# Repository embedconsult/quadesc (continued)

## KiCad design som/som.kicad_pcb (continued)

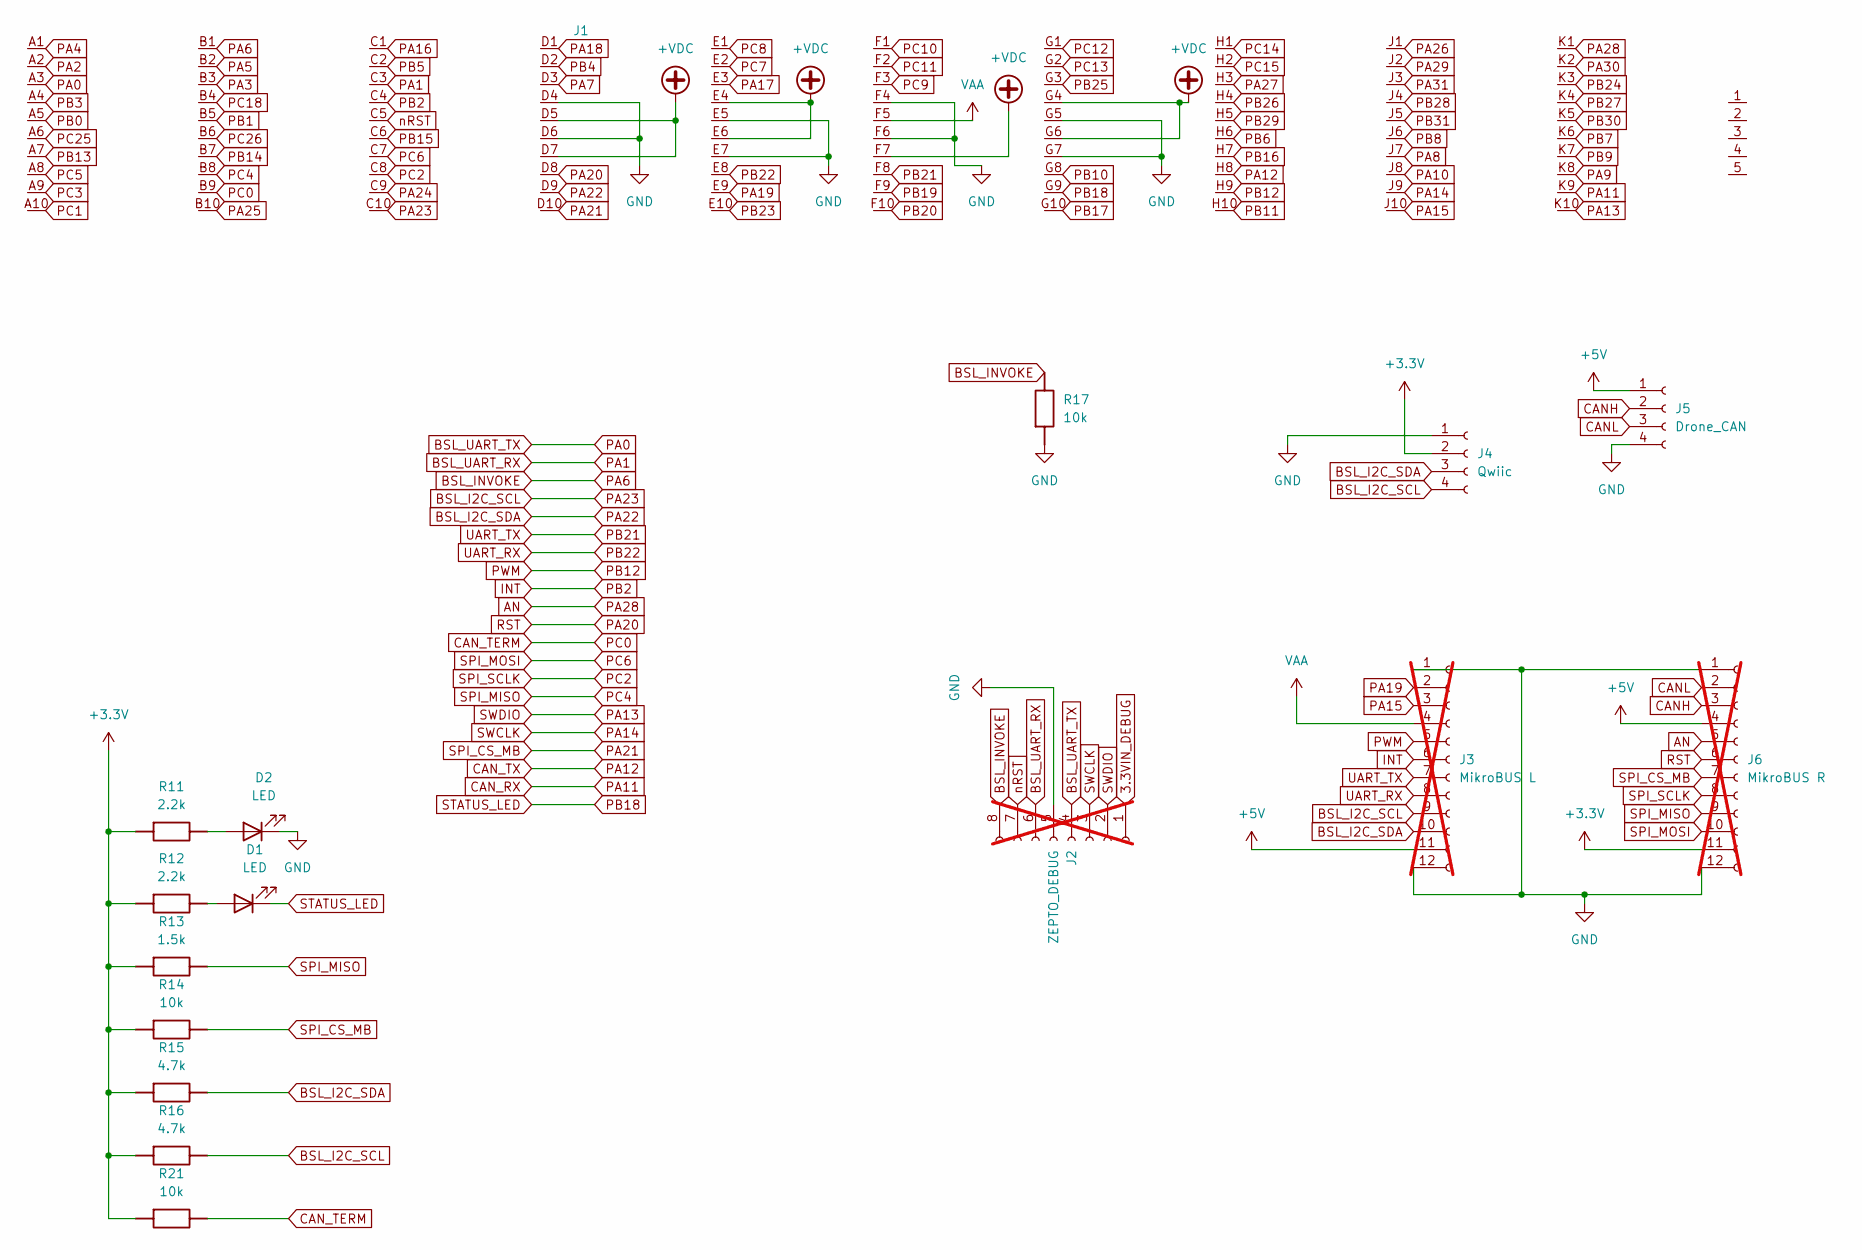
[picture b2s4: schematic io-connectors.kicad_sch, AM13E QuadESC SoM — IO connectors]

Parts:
D1, D2: LED; LED_0402_1005Metric
J1: LGA-100_10x10_14.0x14.0mm
J2: ZEPTO_DEBUG; PinHeader_1x08_P2.54mm_Vertical; not fitted
J3: MikroBUS L; not fitted
J4: Qwiic; CONN_SM04B-SRSS-TB_JST
J5: Drone_CAN; JST_SM04B-GHS-TB
J6: MikroBUS R; not fitted
R11, R12: 2.2k; R_0201_0603Metric
R13: 1.5k; R_0201_0603Metric
R14, R17, R21: 10k; R_0201_0603Metric
R15, R16: 4.7k; R_0201_0603Metric

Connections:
3.3VIN_DEBUG: J2.1; also elsewhere on the board
+3.3V: J4.2, J6.11, R11.1, R12.1, R13.1, R14.1, R15.1, R16.1, R21.1; also elsewhere on the board
+5V: J3.11, J5.1, J6.4; also elsewhere on the board
+VDC: J1.D5, J1.D7, J1.E4, J1.E6, J1.F7, J1.G4, J1.G6; also elsewhere on the board
AN: J1.K1, J6.5; also elsewhere on the board
BSL_I2C_SCL: J1.C10, J3.9, J4.4, R16.2; also elsewhere on the board
BSL_I2C_SDA: J1.D9, J3.10, J4.3, R15.2; also elsewhere on the board
BSL_INVOKE: J1.B1, J2.8, R17.2; also elsewhere on the board
BSL_UART_RX: J1.C3, J2.6; also elsewhere on the board
BSL_UART_TX: J1.A3, J2.4; also elsewhere on the board
CANH: J5.2, J6.3; also elsewhere on the board
CANL: J5.3, J6.2; also elsewhere on the board
CAN_RX: J1.K9; also elsewhere on the board
CAN_TERM: J1.B9, R21.2; also elsewhere on the board
CAN_TX: J1.H8; also elsewhere on the board
GND: D2.1 (K), J1.D4, J1.D6, J1.E5, J1.E7, J1.F4, J1.F6, J1.G5, J1.G7, J2.5, J3.1, J3.12, J4.1, J5.4, J6.1, J6.12, R17.1; also elsewhere on the board
INT: J1.C4, J3.6; also elsewhere on the board
unnamed: D1.2 (A), R12.2
unnamed: D2.2 (A), R11.2
PA2: J1.A2; also elsewhere on the board
PA3: J1.B3; also elsewhere on the board
PA4: J1.A1; also elsewhere on the board
PA5: J1.B2; also elsewhere on the board
PA7: J1.D3; also elsewhere on the board
PA8: J1.J7; also elsewhere on the board
PA9: J1.K8; also elsewhere on the board
PA10: J1.J8; also elsewhere on the board
PA13: J1.K10, J2.2; also elsewhere on the board
PA14: J1.J9, J2.3; also elsewhere on the board
PA15: J1.J10, J3.3; also elsewhere on the board
PA16: J1.C1; also elsewhere on the board
PA17: J1.E3; also elsewhere on the board
PA18: J1.D1; also elsewhere on the board
PA19: J1.E9, J3.2; also elsewhere on the board
PA20: J1.D8, J6.6; also elsewhere on the board
PA21: J1.D10, J6.7, R14.2; also elsewhere on the board
PA24: J1.C9; also elsewhere on the board
PA25: J1.B10; also elsewhere on the board
PA26: J1.J1; also elsewhere on the board
PA27: J1.H3; also elsewhere on the board
PA29: J1.J2; also elsewhere on the board
PA30: J1.K2; also elsewhere on the board
PA31: J1.J3; also elsewhere on the board
PB0: J1.A5; also elsewhere on the board
PB1: J1.B5; also elsewhere on the board
PB3: J1.A4; also elsewhere on the board
PB4: J1.D2; also elsewhere on the board
PB5: J1.C2; also elsewhere on the board
PB6: J1.H6; also elsewhere on the board
PB7: J1.K6; also elsewhere on the board
PB8: J1.J6; also elsewhere on the board
PB9: J1.K7; also elsewhere on the board
PB10: J1.G8; also elsewhere on the board
PB11: J1.H10; also elsewhere on the board
PB12: J1.H9, J3.5; also elsewhere on the board
PB13: J1.A7; also elsewhere on the board
PB14: J1.B7; also elsewhere on the board
PB15: J1.C6; also elsewhere on the board
PB16: J1.H7; also elsewhere on the board
PB17: J1.G10; also elsewhere on the board
PB18: D1.1 (K), J1.G9; also elsewhere on the board
PB19: J1.F9; also elsewhere on the board
PB20: J1.F10; also elsewhere on the board
PB21: J1.F8, J3.7; also elsewhere on the board
PB22: J1.E8, J3.8; also elsewhere on the board
PB23: J1.E10; also elsewhere on the board
PB24: J1.K3; also elsewhere on the board
PB25: J1.G3; also elsewhere on the board
PB26: J1.H4; also elsewhere on the board
PB27: J1.K4; also elsewhere on the board
PB28: J1.J4; also elsewhere on the board
PB29: J1.H5; also elsewhere on the board
PB30: J1.K5; also elsewhere on the board
PB31: J1.J5; also elsewhere on the board
PC1: J1.A10; also elsewhere on the board
PC2: J1.C8, J6.8; also elsewhere on the board
PC3: J1.A9; also elsewhere on the board
PC4: J1.B8, J6.9, R13.2; also elsewhere on the board
PC5: J1.A8; also elsewhere on the board
PC6: J1.C7, J6.10; also elsewhere on the board
PC7: J1.E2; also elsewhere on the board
PC8: J1.E1; also elsewhere on the board
PC9: J1.F3; also elsewhere on the board
PC10: J1.F1; also elsewhere on the board
PC11: J1.F2; also elsewhere on the board
PC12: J1.G1; also elsewhere on the board
PC13: J1.G2; also elsewhere on the board
PC14: J1.H1; also elsewhere on the board
PC15: J1.H2; also elsewhere on the board
PC18: J1.B4; also elsewhere on the board
PC25: J1.A6; also elsewhere on the board
PC26: J1.B6; also elsewhere on the board
VAA: J1.F5, J3.4; also elsewhere on the board
nRST: J1.C5, J2.7; also elsewhere on the board

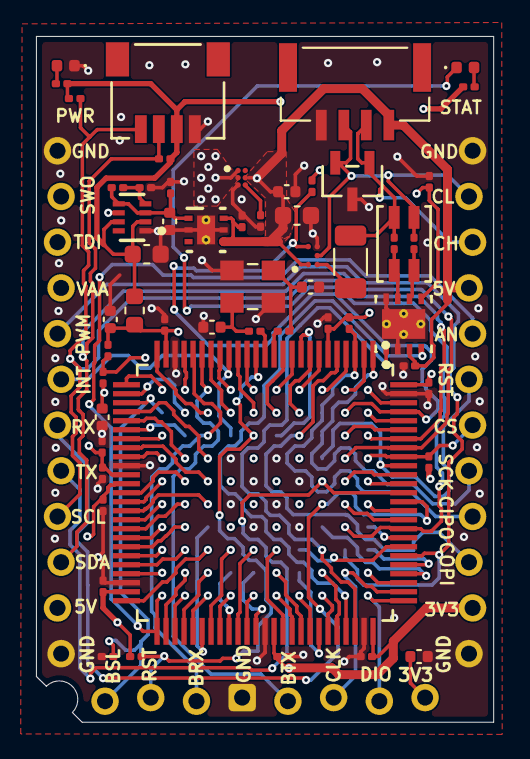
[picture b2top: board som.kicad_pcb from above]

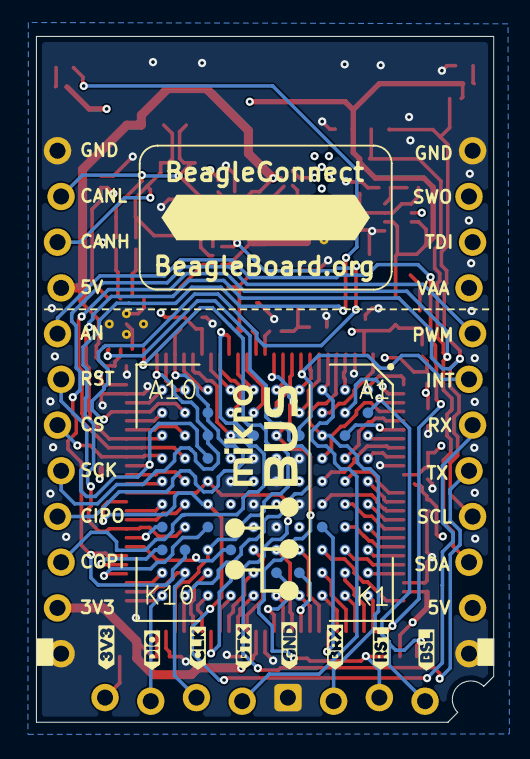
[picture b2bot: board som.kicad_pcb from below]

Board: 4 copper layers, 25.4 x 38.1 mm, 68 parts (10 on the bottom side), 106 nets.

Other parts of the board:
kibuzzard-698ADC7E: G***; kibuzzard-698ADC7E
kibuzzard-698ADC8D: G***; kibuzzard-698ADC8D
kibuzzard-698ADC75: G***; kibuzzard-698ADC75
kibuzzard-698ADC83: G***; kibuzzard-698ADC83
kibuzzard-698ADC88: G***; kibuzzard-698ADC88
kibuzzard-698ADC92: G***; kibuzzard-698ADC92
kibuzzard-698ADC96: G***; kibuzzard-698ADC96
kibuzzard-698AE4C9: G***; kibuzzard-698AE4C9
kibuzzard-698CA76F: G***; kibuzzard-698CA76F

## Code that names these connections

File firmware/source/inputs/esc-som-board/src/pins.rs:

//! Wiring extracted from corrected source 802aacd, current SysConfig v3 authority.
//! Package/mux evidence is recorded separately; chip Pin contains only port/bit.
use am13_rs::gpio::{
    Pin,
    Port::{A, B, C},
};
pub const BSL_UART_TX: Pin = Pin::new(A, 0);
pub const BSL_UART_RX: Pin = Pin::new(A, 1);
pub const BSL_CAN_TX: Pin = Pin::new(A, 12);
pub const BSL_CAN_RX: Pin = Pin::new(A, 11);
pub const BSL_INVOKE: Pin = Pin::new(A, 6);
pub const DRV_ENABLE: Pin = Pin::new(B, 10);
pub const INL_ENABLE: Pin = Pin::new(B, 11);
pub const STATUS_LED: Pin = Pin::new(B, 18);
pub const CAN_TERM: Pin = Pin::new(B, 9);
pub const I2C_SDA: Pin = Pin::new(A, 22);
pub const I2C_SCL: Pin = Pin::new(A, 23);
pub const SPI_MOSI: Pin = Pin::new(C, 6);
pub const SPI_MISO: Pin = Pin::new(C, 4);
pub const SPI_SCLK: Pin = Pin::new(C, 2);
pub const NFAULT: [Pin; 4] = [
    Pin::new(A, 30),
    Pin::new(B, 15),
    Pin::new(B, 17),
    Pin::new(B, 0),
];
pub const DRIVER_CS: [Pin; 4] = [
    Pin::new(C, 13),
    Pin::new(B, 14),
    Pin::new(B, 16),
    Pin::new(C, 5),
];

/// All motor PWM pads from v3, including the extra Motor1 3B output.
/// LED-cal holds these as GPIO-low; it never selects the PWM mux.
pub const MOTOR_OUTPUTS: [Pin; 13] = [
    Pin::new(B, 6),
    Pin::new(B, 7),
    Pin::new(B, 8),
    Pin::new(B, 12),
    Pin::new(C, 25),
    Pin::new(C, 26),
    Pin::new(C, 18),
    Pin::new(B, 13),
    Pin::new(A, 10),
    Pin::new(A, 25),
    Pin::new(C, 1),
    Pin::new(C, 3),
    Pin::new(A, 24),
];
/// (pad, mux, MCPWM module, output index 0..5 for 1A,1B,2A,2B,3A,3B).
/// v3 contains only these 13 motor outputs; MCPWM4 DSHOT/buzzer routes are excluded.
pub const PWM_ROUTES: [(Pin, u8, u8, u8); 13] = [
    (Pin::new(B, 13), 5, 0, 1),
    (Pin::new(A, 10), 7, 0, 4),
    (Pin::new(A, 25), 13, 0, 5),
    (Pin::new(B, 6), 5, 1, 0),
    (Pin::new(B, 7), 5, 1, 2),
    (Pin::new(B, 8), 5, 1, 4),
    (Pin::new(B, 12), 5, 1, 5),
    (Pin::new(C, 1), 7, 2, 0),
    (Pin::new(C, 3), 7, 2, 2),
    (Pin::new(A, 24), 3, 2, 4),
    (Pin::new(C, 25), 4, 3, 0),
    (Pin::new(C, 26), 4, 3, 2),
    (Pin::new(C, 18), 4, 3, 4),
];
pub const DSHOT_INPUTS: [Pin; 4] = [
    Pin::new(A, 27),
    Pin::new(A, 4),
    Pin::new(B, 28),
    Pin::new(A, 26),
];
